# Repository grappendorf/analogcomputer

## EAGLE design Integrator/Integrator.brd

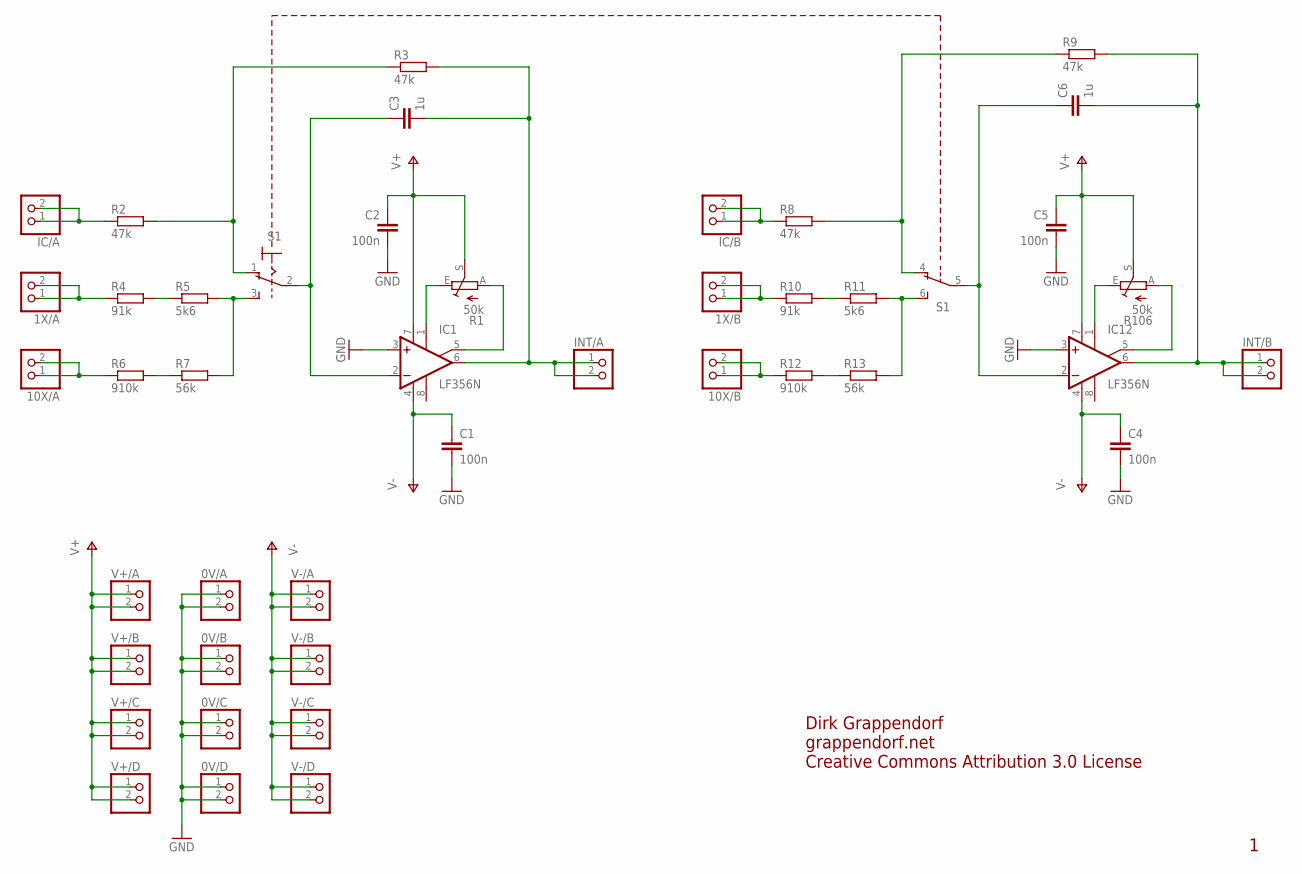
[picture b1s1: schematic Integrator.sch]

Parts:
0V/A, 0V/B, 0V/C, 0V/D, 1X/A, 1X/B, 10X/A, 10X/B: PINHD-1X2; 1X02
C1, C2, C4, C5: 100n; C025-025X050
C3, C6: 1u; C050-035X075
IC1, IC12: LF356N; DIL08
IC/A: PINHD-1X2; 1X02
IC/B: PINHD-1X2; 1X02
INT/A: PINHD-1X2; 1X02
INT/B: PINHD-1X2; 1X02
R1, R106: 50k; LI15
R2, R3, R8, R9: 47k; 0207/7
R4, R10: 91k; 0207/7
R5, R11: 5k6; 0207/7
R6, R12: 910k; 0207/7
R7, R13: 56k; 0207/7
S1: REICHELT-MS_500H
V+/A: PINHD-1X2; 1X02
V+/B: PINHD-1X2; 1X02
V+/C: PINHD-1X2; 1X02
V+/D: PINHD-1X2; 1X02
V-/A: PINHD-1X2; 1X02
V-/B: PINHD-1X2; 1X02
V-/C: PINHD-1X2; 1X02
V-/D: PINHD-1X2; 1X02

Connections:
GND: 0V/A.1, 0V/A.2, 0V/B.1, 0V/B.2, 0V/C.1, 0V/C.2, 0V/D.1, 0V/D.2, C1.2, C2.2, C4.2, C5.2, IC1.3 (+IN), IC12.3 (+IN)
unnamed: IC1.1 (ON1), R1.E
unnamed: IC1.5 (ON2), R1.A
unnamed: C3.2, IC1.6 (OUT), INT/A.1, INT/A.2, R3.2
unnamed: C3.1, IC1.2 (-IN), S1.2
unnamed: 10X/A.1, 10X/A.2, R6.1
unnamed: 1X/A.1, 1X/A.2, R4.1
unnamed: IC/A.1, IC/A.2, R2.1
unnamed: IC12.1 (ON1), R106.E
unnamed: IC12.5 (ON2), R106.A
unnamed: C6.2, IC12.6 (OUT), INT/B.1, INT/B.2, R9.2
unnamed: C6.1, IC12.2 (-IN), S1.5
unnamed: 1X/B.1, 1X/B.2, R10.1
unnamed: 10X/B.1, 10X/B.2, R12.1
unnamed: IC/B.1, IC/B.2, R8.1
unnamed: R4.2, R5.1
unnamed: R6.2, R7.1
unnamed: R10.2, R11.1
unnamed: R12.2, R13.1
unnamed: R5.2, R7.2, S1.3 (S)
unnamed: R11.2, R13.2, S1.6 (S)
unnamed: R2.2, R3.1, S1.1 (O)
unnamed: R8.2, R9.1, S1.4 (O)
V+: C2.1, C5.1, IC1.7 (V+), IC12.7 (V+), R1.S, R106.S, V+/A.1, V+/A.2, V+/B.1, V+/B.2, V+/C.1, V+/C.2, V+/D.1, V+/D.2
V-: C1.1, C4.1, IC1.4 (V-), IC12.4 (V-), V-/A.1, V-/A.2, V-/B.1, V-/B.2, V-/C.1, V-/C.2, V-/D.1, V-/D.2

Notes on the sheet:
Dirk Grappendorf
grappendorf.net
Creative Commons Attribution 3.0 License

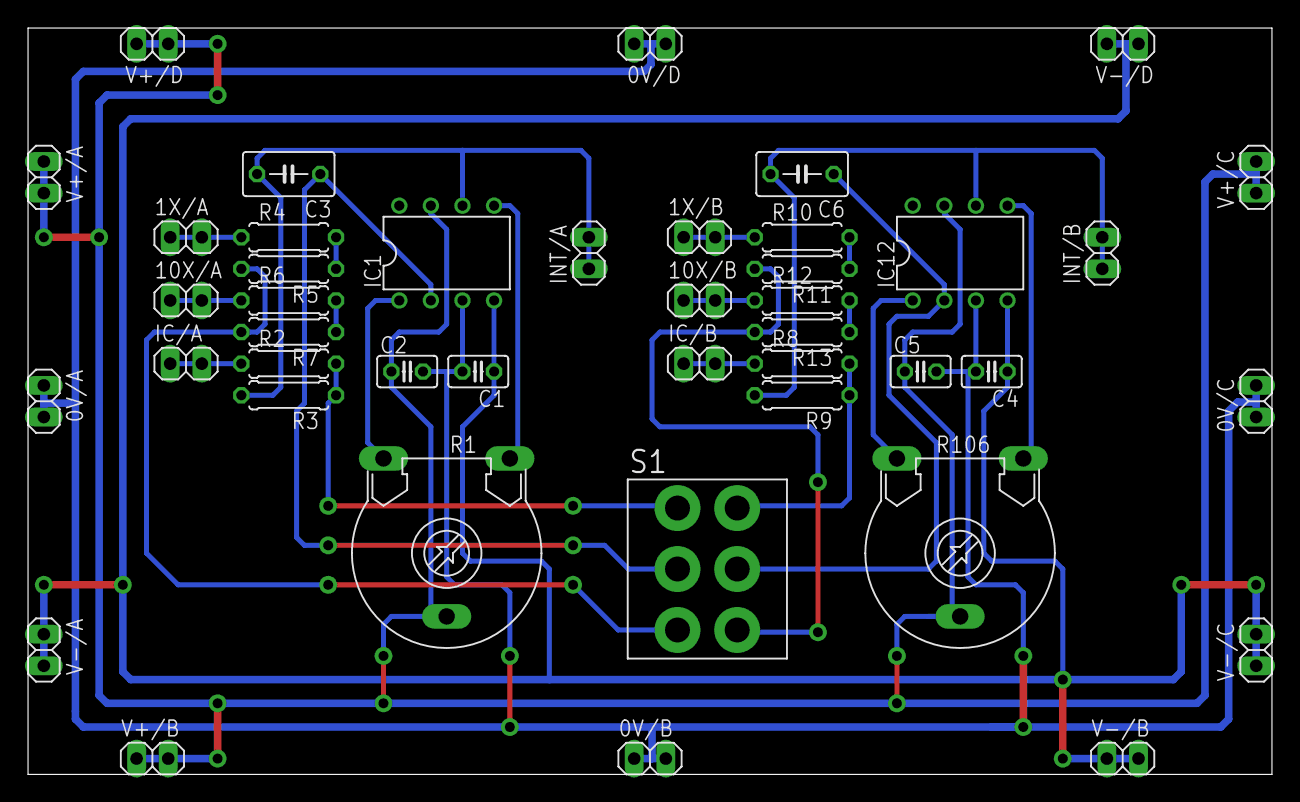
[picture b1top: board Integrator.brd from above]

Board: 2 copper layers, 100.0 x 60.0 mm, 43 parts (0 on the bottom side), 25 nets.
